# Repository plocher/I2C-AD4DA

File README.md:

# I2C-AD4DA
## License: CERN Open Hardware Licence v1.2

## Status: mature

I2C 4x A/D 1x  D/A I/O expander based on a PCF8591T

Expansion card that provides four Analog to Digital inputs and one digital to analog output.
I use it to control LED Layout lighting color balances and levels with slide potentiometers.

## Versions:
 * 1.0
 * 1.1
 * 2.0
 * 3.0

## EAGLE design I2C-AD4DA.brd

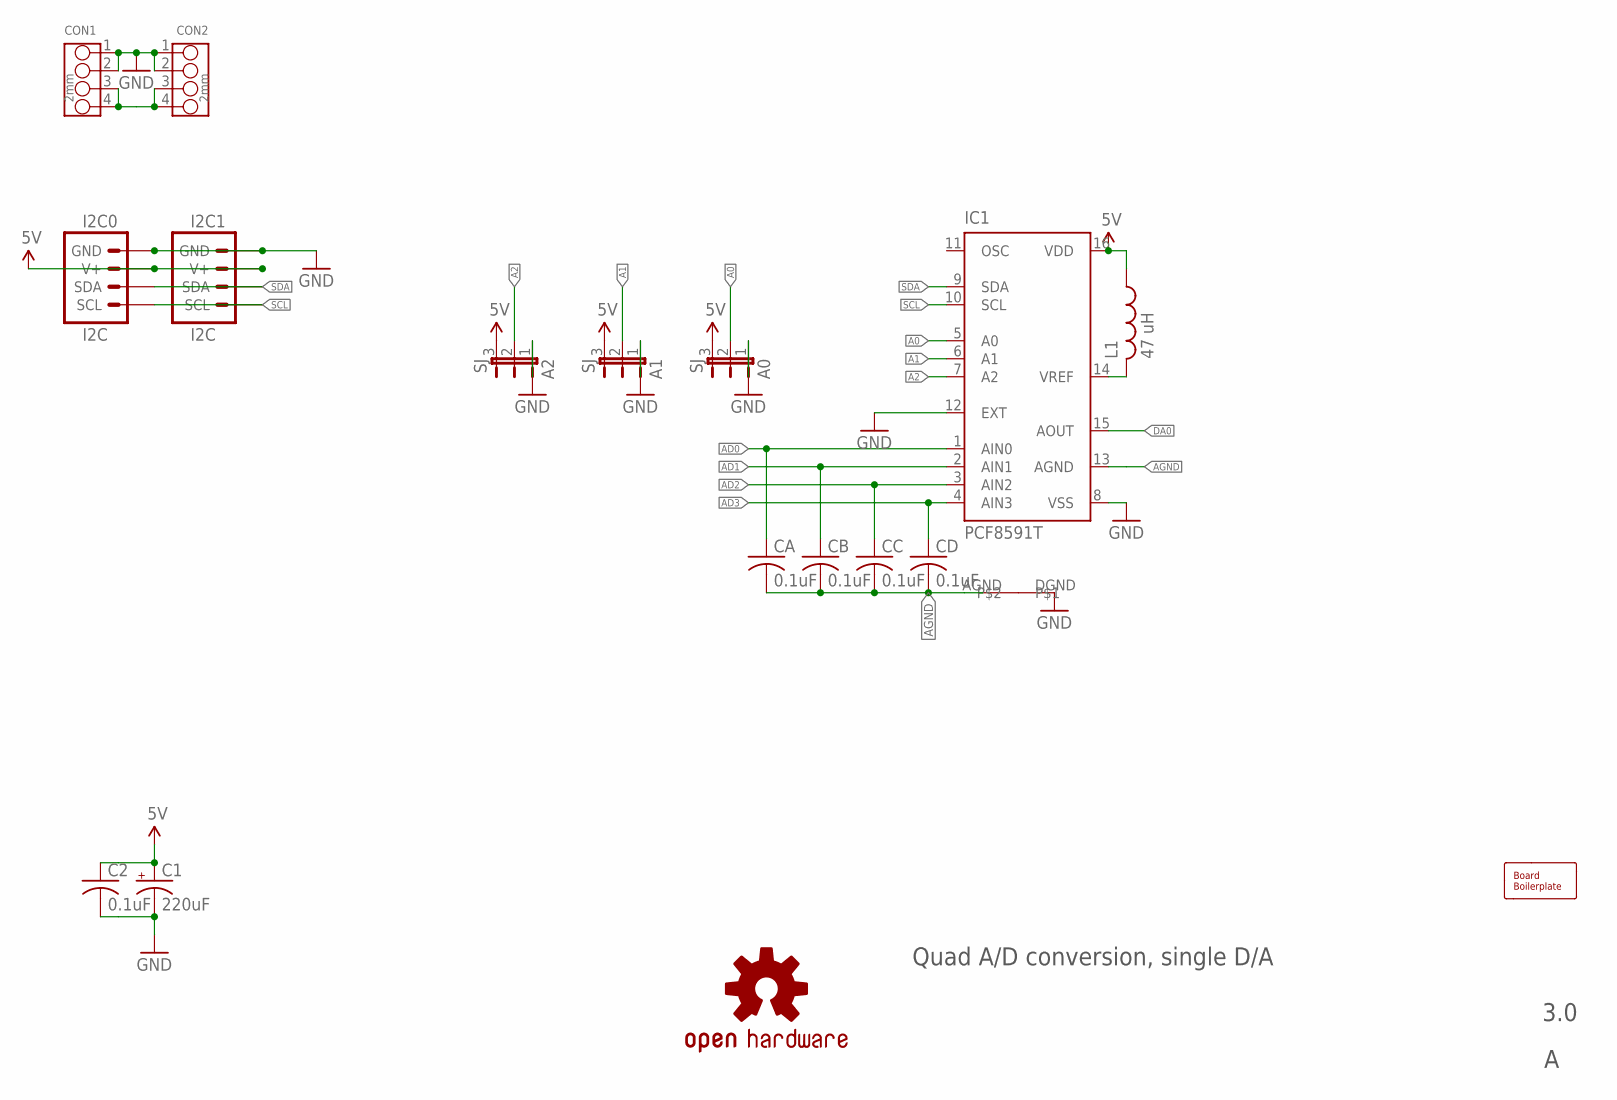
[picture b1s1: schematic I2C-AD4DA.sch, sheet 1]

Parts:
A0, A1, A2: SJ; SJ_3_PASTE1&2
BOARD1: BOARD; BOARD-DINRAIL-3.17INX10CM
C1: 220uF; 0810-CAP
C2: 0.1uF; 0805-CAP
CA: 0.1uF; 0805-CAP
CB: 0.1uF; 0805-CAP
CC: 0.1uF; 0805-CAP
CD: 0.1uF; 0805-CAP
CON1, CON2: 2mm; 4P-2.0
I2C0, I2C1: I2C; I2C-L
IC1: PCF8591T; SO16W
L1: 47 uH; L2012C
LOGO1: OSHW; OSHW-LOGO-L
U$1: AGND+DGND

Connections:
5V: A0.3, A1.3, A2.3, C1.+, C2.1, I2C0.V+, I2C0.V+@1 (V+), I2C1.V+, I2C1.V+@1 (V+), IC1.16 (VDD), L1.1; also elsewhere on the board
A0: A0.2, IC1.5 (A0)
A1: A1.2, IC1.6 (A1)
A2: A2.2, IC1.7 (A2)
AD0: CA.1, IC1.1 (AIN0); also elsewhere on the board
AD1: CB.1, IC1.2 (AIN1); also elsewhere on the board
AD2: CC.1, IC1.3 (AIN2); also elsewhere on the board
AD3: CD.1, IC1.4 (AIN3); also elsewhere on the board
AGND: CA.2, CB.2, CC.2, CD.2, IC1.13 (AGND), U$1.AGND; also elsewhere on the board
DA0: IC1.15 (AOUT)
GND: A0.1, A1.1, A2.1, C1.-, C2.2, CON1.1, CON1.2, CON2.1, CON2.2, I2C0.GND, I2C0.GND@1 (GND), I2C1.GND, I2C1.GND@1 (GND), IC1.8 (VSS), IC1.12 (EXT), U$1.DGND; also elsewhere on the board
unnamed: IC1.14 (VREF), L1.2
SCL: I2C0.SCL, I2C0.SCL@1 (SCL), I2C1.SCL, I2C1.SCL@1 (SCL), IC1.10 (SCL)
SDA: I2C0.SDA, I2C0.SDA@1 (SDA), I2C1.SDA, I2C1.SDA@1 (SDA), IC1.9 (SDA)
VIN: CON1.3, CON1.4, CON2.3, CON2.4

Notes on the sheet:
Quad A/D conversion, single D/A
3.0

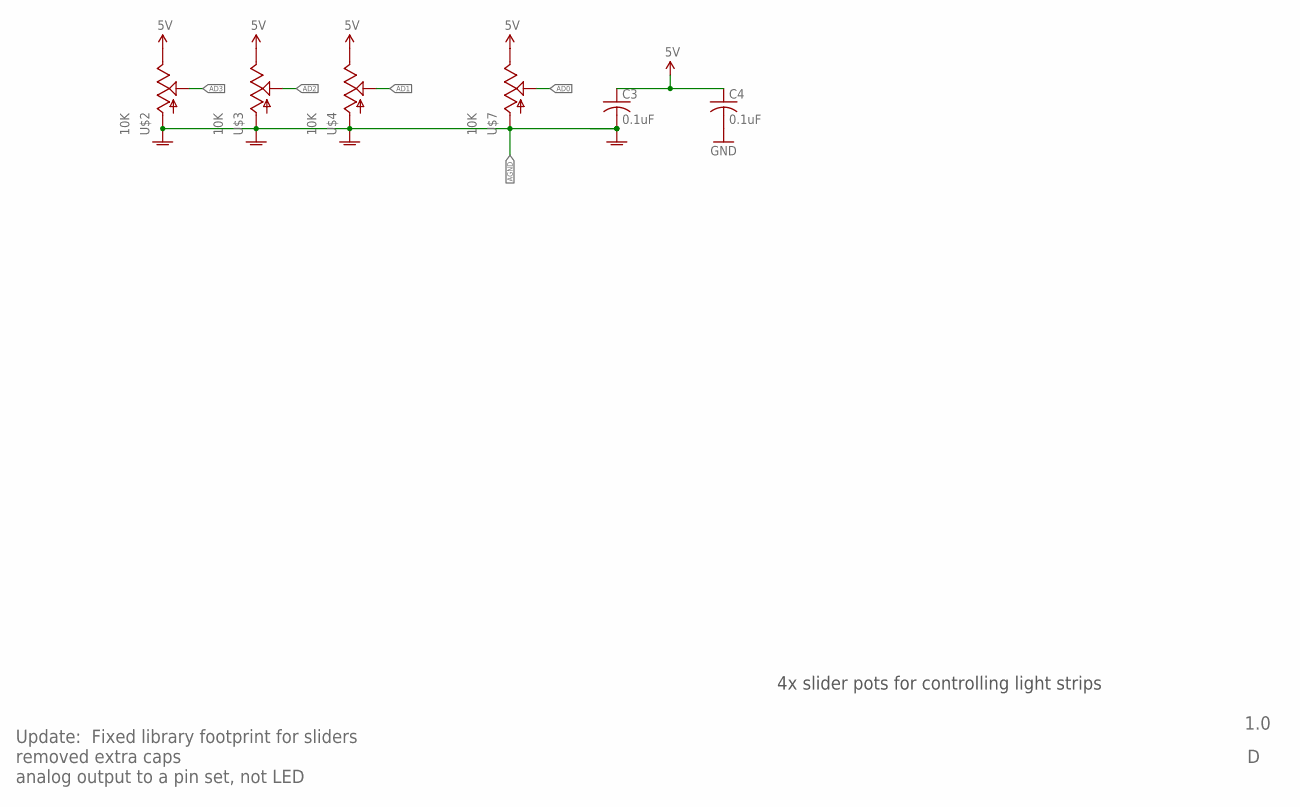
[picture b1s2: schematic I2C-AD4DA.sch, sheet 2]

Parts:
C3, C4: 0.1uF; 0805-CAP
U$2, U$3, U$4, U$7: 10K; SLIDER-45MM

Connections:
5V: C3.1, C4.1, U$2.E, U$3.E, U$4.E, U$7.E; also elsewhere on the board
AD0: U$7.S; also elsewhere on the board
AD1: U$4.S; also elsewhere on the board
AD2: U$3.S; also elsewhere on the board
AD3: U$2.S; also elsewhere on the board
AGND: C3.2, U$2.A, U$2.AGND@0 (AGND), U$2.AGND@1 (AGND), U$3.A, U$3.AGND@0 (AGND), U$3.AGND@1 (AGND), U$4.A, U$4.AGND@0 (AGND), U$4.AGND@1 (AGND), U$7.A, U$7.AGND@0 (AGND), U$7.AGND@1 (AGND); also elsewhere on the board
GND: C4.2; also elsewhere on the board

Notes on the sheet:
4x slider pots for controlling light strips
1.0
Update: Fixed library footprint for sliders removed extra caps analog output to a pin set, not LED

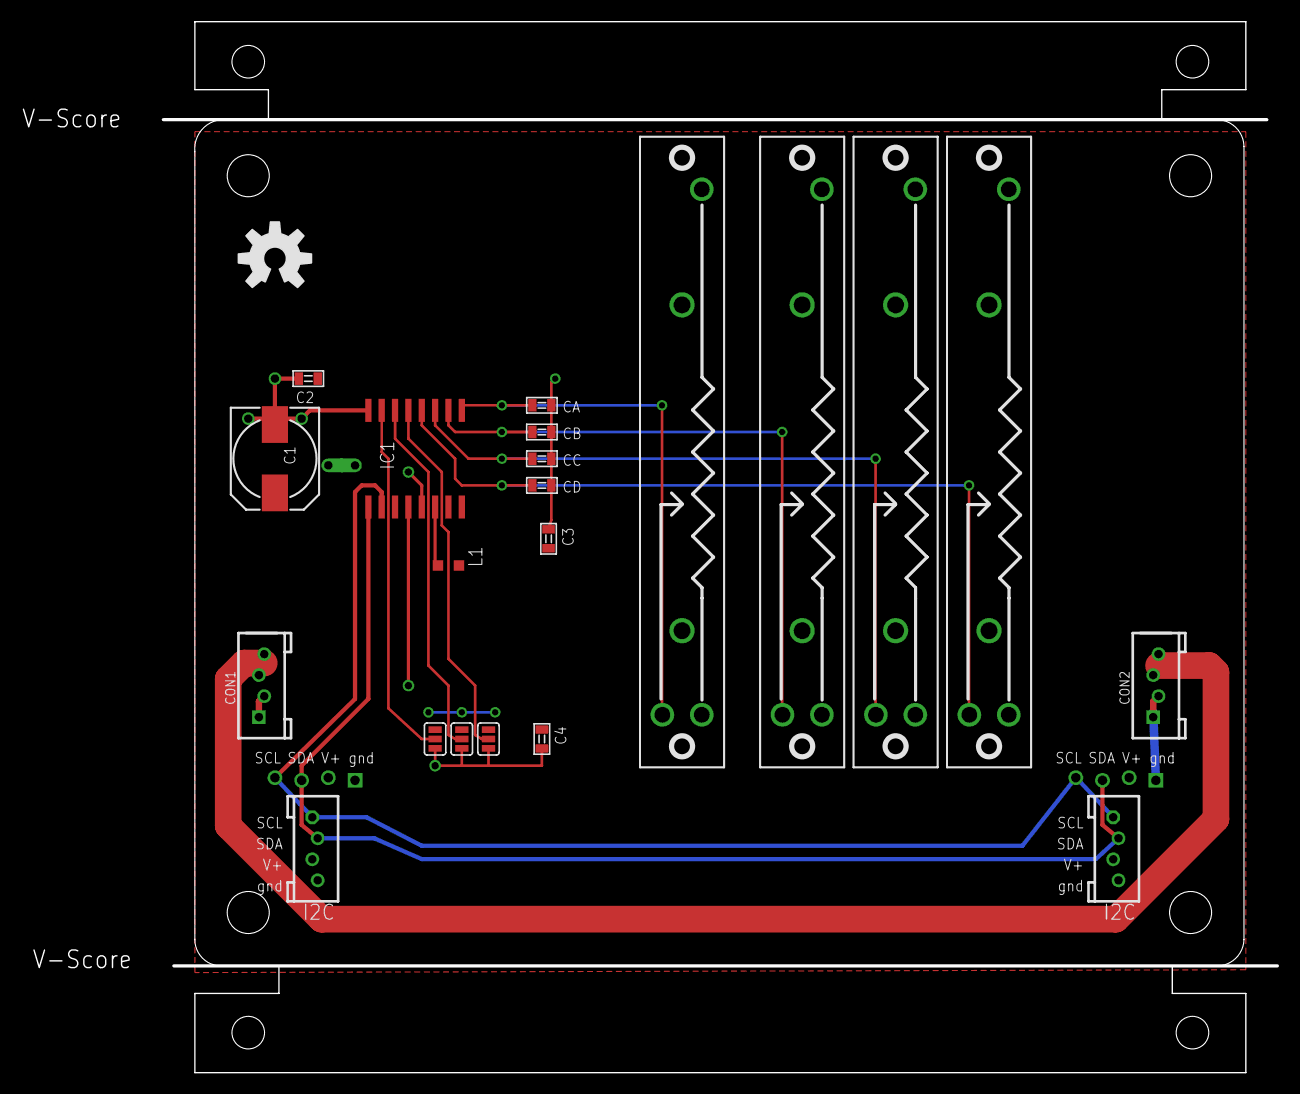
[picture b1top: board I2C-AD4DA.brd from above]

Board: 2 copper layers, 119.4 x 99.8 mm, 24 parts (0 on the bottom side), 14 nets.

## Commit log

2019-12-08 added graphic
2020-05-04 updated tags
2020-10-05 added values for connectors
2020-10-06 normalized values

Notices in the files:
parts and their libraries:
SparkFun-Aesthetics: Licensing: CC v3.0 Share-Alike You are welcome to use this library for commercial purposes.
SPCoast: http://freedomdefined.org/OSHW Creative Commons - Attribution - ShareAlike 3.0
